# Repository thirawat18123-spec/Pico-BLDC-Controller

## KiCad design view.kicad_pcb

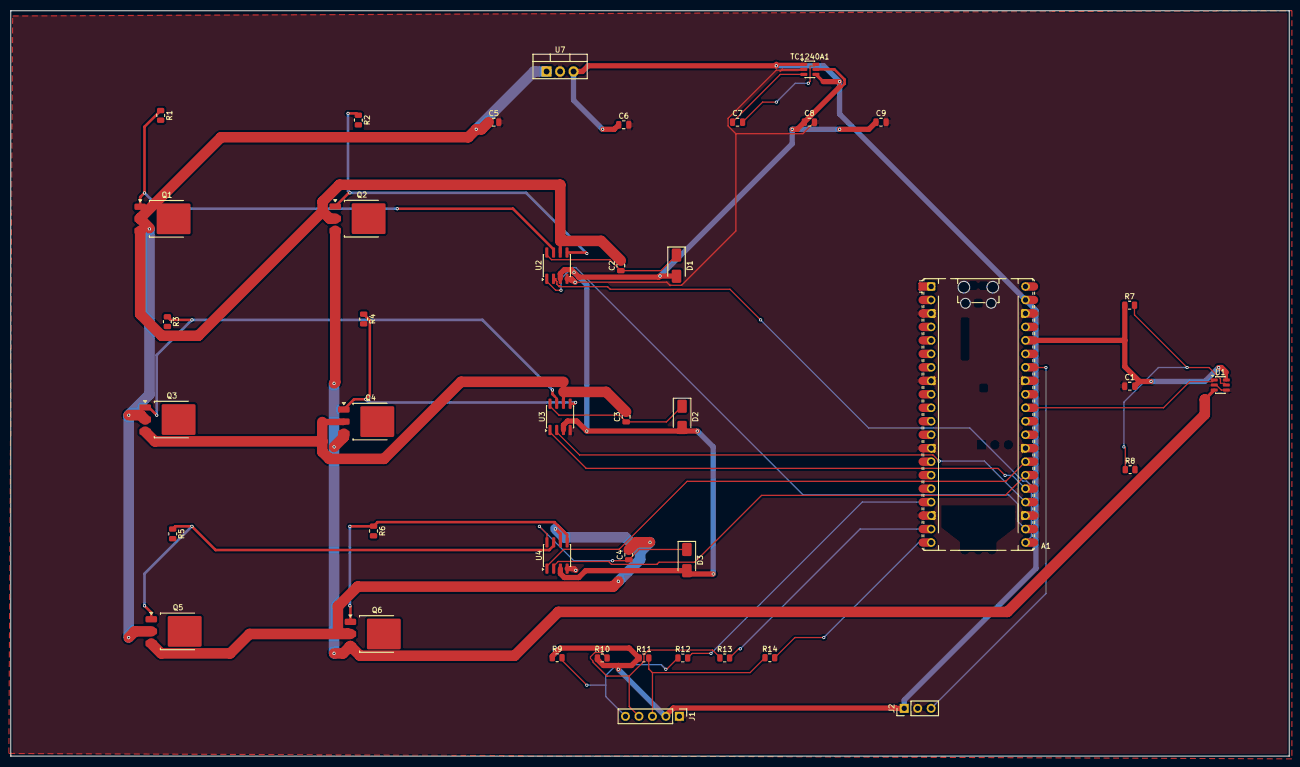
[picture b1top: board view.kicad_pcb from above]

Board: 2 copper layers, 241.0 x 140.5 mm, 41 parts (0 on the bottom side), 35 nets.

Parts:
A1: RaspberryPi_Pico; RaspberryPi_Pico_Common_Unspecified
C1, C2, C3, C4, C5, C6, C7, C8, C9: 1uF; C_0805_2012Metric
D1, D2, D3: D; D_SMA
J1: Conn_01x05; PinHeader_1x05_P2.54mm_Vertical
J2: Conn_01x03; PinHeader_1x03_P2.54mm_Vertical
Q1, Q2, Q3, Q4, Q5, Q6: Q_NMOS; TO-252-3_TabPin2
R1, R2, R3, R4, R5, R6: 22; R_0805_2012Metric
R7, R8: 47k; R_0805_2012Metric
R9, R10, R11, R12, R13, R14: 2.2k; R_0805_2012Metric
TC1240A1: SOT-23-6
U1: INA181; SOT-23-6
U2, U3, U4: SOIC-8_3.9x4.9mm_P1.27mm
U7: L7805; TO-220-3_Vertical

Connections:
+3.3V: A1.36 (3V3), C1.2, R7.1, U1.6 (V+)
+5V: A1.39 (VSYS), C6.1, J1.2, J2.1, R9.1, R10.1, R11.1, TC1240A1.1 (VIN1), TC1240A1.4 (SHDN), U7.3 (OUT)
/10V: C8.1, C9.1, D1.2 (A), D2.2 (A), D3.2 (A), TC1240A1.5 (VOUT), U2.3 (VCC), U3.3 (VCC), U4.3 (VCC)
/COM_A: C2.2, Q1.3, Q2.2, U2.6 (VS)
/COM_B: C3.2, Q3.3, Q4.2, U3.6 (VS)
/COM_C: C4.2, Q5.3, Q6.2, U4.6 (VS)
/CTRL_AH: A1.21 (GPIO16), U2.2 (HIN)
/CTRL_AL: A1.22 (GPIO17), U2.1 (LIN)
/CTRL_BH: A1.24 (GPIO18), U3.2 (HIN)
/CTRL_BL: A1.25 (GPIO19), U3.1 (LIN)
/CTRL_CH: A1.26 (GPIO20), U4.2 (HIN)
/CTRL_CL: A1.27 (GPIO21), U4.1 (LIN)
/DRV_AH: Q1.1, R1.1, U2.7 (HO)
/DRV_AL: Q2.1, R2.1, U2.5 (LO)
/DRV_BH: Q3.1, R3.1, U3.7 (HO)
/DRV_BL: Q4.1, R4.1, U3.5 (LO)
/DRV_CH: Q5.1, R5.1, U4.7 (HO)
/DRV_CL: Q6.1, R6.1, U4.5 (LO)
/HALL_A: A1.17 (GPIO13), R12.2
/HALL_B: A1.19 (GPIO14), R13.2
/HALL_C: A1.20 (GPIO15), R14.2
/ISENSE: A1.31 (GPIO26_ADC0), U1.1
/SHUNT+: Q2.3, Q4.3, Q6.3, U1.3 (+)
/THROTTLE: A1.34 (GPIO28_ADC2), J2.3
/V_RAW: C5.1, Q1.2, Q3.2, Q5.2, U7.1 (IN)
GND: A1.3 (GND), A1.8 (GND), A1.13 (GND), A1.18 (GND), A1.23 (GND), A1.28 (GND), A1.33 (AGND), A1.38 (GND), C1.1, C5.2, C6.2, C8.2, C9.2, J1.1, J2.2, R8.2, TC1240A1.2 (GND), U1.2 (GND), U1.4 (-), U2.4 (GND), U3.4 (GND), U4.4 (GND), U7.2 (GND)
unnamed: C2.1, D1.1 (K), U2.8 (VB)
unnamed: C3.1, D2.1 (K), U3.8 (VB)
unnamed: C4.1, D3.1 (K), U4.8 (VB)
unnamed: J1.3, R11.2, R14.1
unnamed: J1.4, R10.2, R13.1
unnamed: J1.5, R9.2, R12.1
unnamed: C7.2, TC1240A1.6 (C+)
unnamed: C7.1, TC1240A1.3 (C-)
unnamed: R7.2, R8.1, U1.5 (REF)
